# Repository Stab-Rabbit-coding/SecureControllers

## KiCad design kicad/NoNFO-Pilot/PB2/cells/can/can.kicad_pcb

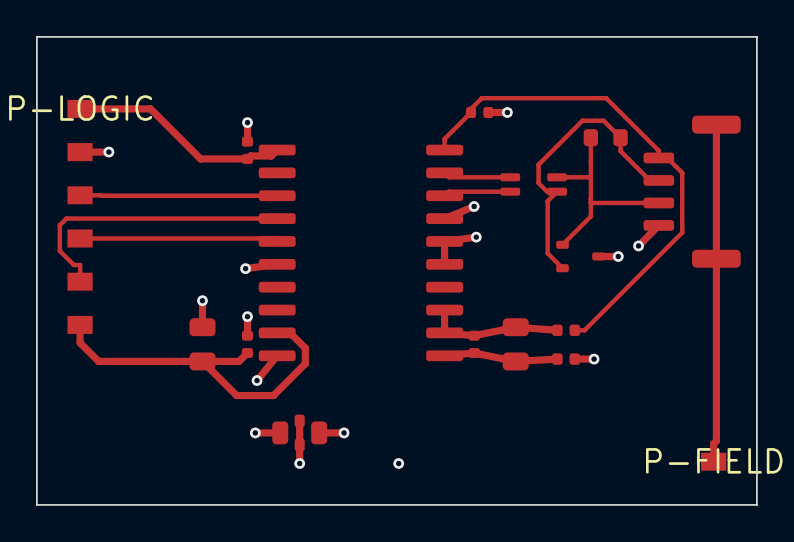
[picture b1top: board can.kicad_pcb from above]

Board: 4 copper layers, 40.0 x 26.0 mm, 16 parts (0 on the bottom side), 15 nets.

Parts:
C-CAN1, C-CAN4: 10nF; C_0402_1005Metric
C-CAN2, C-CAN5: 10uF 10V X5R; C_0805_2012Metric
C-CAN3, C-CAN6: 100nF; C_0402_1005Metric
CAN-FD: SM04B-GHS-TB; JST_GH_SM04B-GHS-TB_1x04-1MP_P1.25mm_Horizontal
CAN-TR: ISOW1044BDFMR; SOIC-20W_7.5x12.8mm_P1.27mm
CHK-CAN: SRF2012-100Y; Bourns_SRF2012_4T
FB-CAN-G: 330R@100MHz; L_0402_1005Metric
FB-CAN-V: 330R@100MHz; L_0402_1005Metric
P-FIELD: cell port; Port_1x1
P-LOGIC: cell port; Port_6x1
R-CANT: 120R; R_0603_1608Metric
TVS-CAN: ESD2CAN24-Q1; SOT-323_SC-70
X2Y-CAN: 4.7nF X2Y; X2Y_0805_4T

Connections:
+3V3: C-CAN3.1, CAN-TR.1, P-LOGIC.1
+5V: C-CAN1.1, C-CAN2.1, CAN-TR.9, P-LOGIC.6
CAN_H: CAN-TR.19, CHK-CAN.1
CAN_H_F: CAN-FD.2, CHK-CAN.2, R-CANT.1, TVS-CAN.1
CAN_L: CAN-TR.18, CHK-CAN.4
CAN_L_F: CAN-FD.3, CHK-CAN.3, R-CANT.2, TVS-CAN.2
CAN_STB: CAN-TR.4, P-LOGIC.5
GND: C-CAN1.2, C-CAN2.2, C-CAN3.2, CAN-TR.6, CAN-TR.10, P-LOGIC.2, X2Y-CAN.1, X2Y-CAN.2
GND2_CAN: C-CAN6.2, CAN-FD.1, CAN-TR.15, CAN-TR.16, CAN-TR.17, FB-CAN-G.2, TVS-CAN.3, X2Y-CAN.3, X2Y-CAN.4
GND2_CAN_DCDC: C-CAN4.2, C-CAN5.2, CAN-TR.11, FB-CAN-G.1
MCAN_RX: CAN-TR.5, P-LOGIC.4
MCAN_TX: CAN-TR.3, P-LOGIC.3
PGND: CAN-FD.MP, P-FIELD.1
VCC2_CAN: C-CAN6.1, CAN-FD.4, CAN-TR.20, FB-CAN-V.2
VCC2_CAN_DCDC: C-CAN4.1, C-CAN5.1, CAN-TR.12, CAN-TR.13, FB-CAN-V.1

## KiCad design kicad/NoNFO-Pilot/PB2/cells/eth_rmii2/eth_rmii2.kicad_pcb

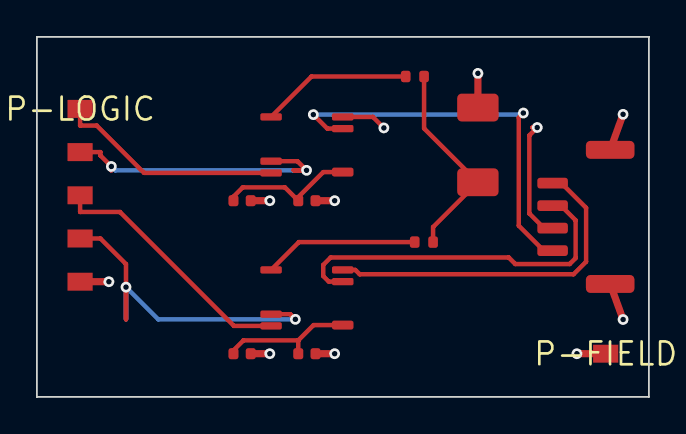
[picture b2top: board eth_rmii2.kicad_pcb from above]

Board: 4 copper layers, 34.0 x 20.0 mm, 12 parts (0 on the bottom side), 15 nets.

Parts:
C-RMII2-BS: 10nF 2kV; C_1808_4520Metric
C-RMII2-CRD1, C-RMII2-CTD1: 100nF; C_0402_1005Metric
C-RMII2-CRD2, C-RMII2-CTD2: 1uF; C_0402_1005Metric
J-ETH-RMII2: SM04B-GHS-TB; JST_GH_SM04B-GHS-TB_1x04-1MP_P1.25mm_Horizontal
P-FIELD: cell port; Port_1x1
P-LOGIC: cell port; Port_5x1
R-RMII2-BSR, R-RMII2-BST: 75R; R_0402_1005Metric
T-RMII2-RX, T-RMII2-TX: TC1G00; Pulse_TC1G00_PulseChip_4.7x3.2mm

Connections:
ETH_RMII2_BS: C-RMII2-BS.1, R-RMII2-BSR.2, R-RMII2-BST.2
ETH_RMII2_CRD: C-RMII2-CRD1.1, C-RMII2-CRD2.1, T-RMII2-RX.7
ETH_RMII2_CTD: C-RMII2-CTD1.1, C-RMII2-CTD2.1, T-RMII2-TX.7
ETH_RMII2_LINE_CRX: R-RMII2-BSR.1, T-RMII2-RX.3
ETH_RMII2_LINE_CTX: R-RMII2-BST.1, T-RMII2-TX.3
ETH_RMII2_LINE_RXN: J-ETH-RMII2.4, T-RMII2-RX.5
ETH_RMII2_LINE_RXP: J-ETH-RMII2.3, T-RMII2-RX.6
ETH_RMII2_LINE_TXN: J-ETH-RMII2.2, T-RMII2-TX.5
ETH_RMII2_LINE_TXP: J-ETH-RMII2.1, T-RMII2-TX.6
ETH_RMII2_RXN: P-LOGIC.4, T-RMII2-RX.2
ETH_RMII2_RXP: P-LOGIC.3, T-RMII2-RX.1
ETH_RMII2_TXN: P-LOGIC.2, T-RMII2-TX.2
ETH_RMII2_TXP: P-LOGIC.1, T-RMII2-TX.1
GND: C-RMII2-CRD1.2, C-RMII2-CRD2.2, C-RMII2-CTD1.2, C-RMII2-CTD2.2, P-LOGIC.5
PGND: C-RMII2-BS.2, J-ETH-RMII2.MP, P-FIELD.1

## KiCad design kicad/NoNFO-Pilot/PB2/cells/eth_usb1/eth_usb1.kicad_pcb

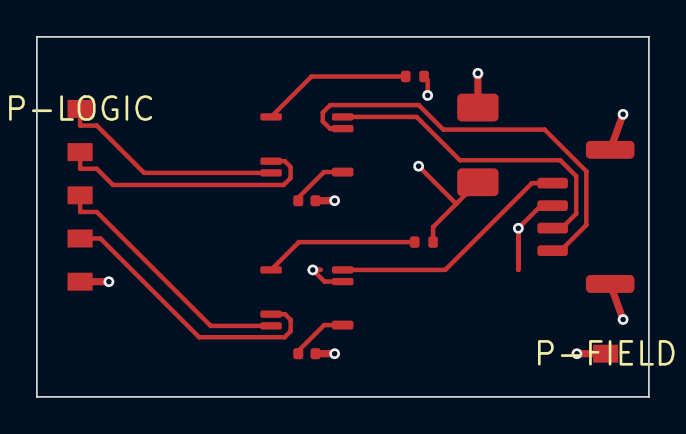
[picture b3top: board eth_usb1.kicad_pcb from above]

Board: 4 copper layers, 34.0 x 20.0 mm, 10 parts (0 on the bottom side), 15 nets.

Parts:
C-USB1-BS: 10nF 2kV; C_1808_4520Metric
C-USB1-CRD, C-USB1-CTD: 100nF; C_0402_1005Metric
J-ETH-USB1: SM04B-GHS-TB; JST_GH_SM04B-GHS-TB_1x04-1MP_P1.25mm_Horizontal
P-FIELD: cell port; Port_1x1
P-LOGIC: cell port; Port_5x1
R-USB1-BSR, R-USB1-BST: 75R; R_0402_1005Metric
T-USB1-RX, T-USB1-TX: TC1G00; Pulse_TC1G00_PulseChip_4.7x3.2mm

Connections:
ETH_USB1_BS: C-USB1-BS.1, R-USB1-BSR.2, R-USB1-BST.2
ETH_USB1_CRD: C-USB1-CRD.1, T-USB1-RX.7
ETH_USB1_CTD: C-USB1-CTD.1, T-USB1-TX.7
ETH_USB1_LINE_CRX: R-USB1-BSR.1, T-USB1-RX.3
ETH_USB1_LINE_CTX: R-USB1-BST.1, T-USB1-TX.3
ETH_USB1_LINE_RXN: J-ETH-USB1.4, T-USB1-RX.5
ETH_USB1_LINE_RXP: J-ETH-USB1.3, T-USB1-RX.6
ETH_USB1_LINE_TXN: J-ETH-USB1.2, T-USB1-TX.5
ETH_USB1_LINE_TXP: J-ETH-USB1.1, T-USB1-TX.6
ETH_USB1_RXN: P-LOGIC.4, T-USB1-RX.2
ETH_USB1_RXP: P-LOGIC.3, T-USB1-RX.1
ETH_USB1_TXN: P-LOGIC.2, T-USB1-TX.2
ETH_USB1_TXP: P-LOGIC.1, T-USB1-TX.1
GND: C-USB1-CRD.2, C-USB1-CTD.2, P-LOGIC.5
PGND: C-USB1-BS.2, J-ETH-USB1.MP, P-FIELD.1

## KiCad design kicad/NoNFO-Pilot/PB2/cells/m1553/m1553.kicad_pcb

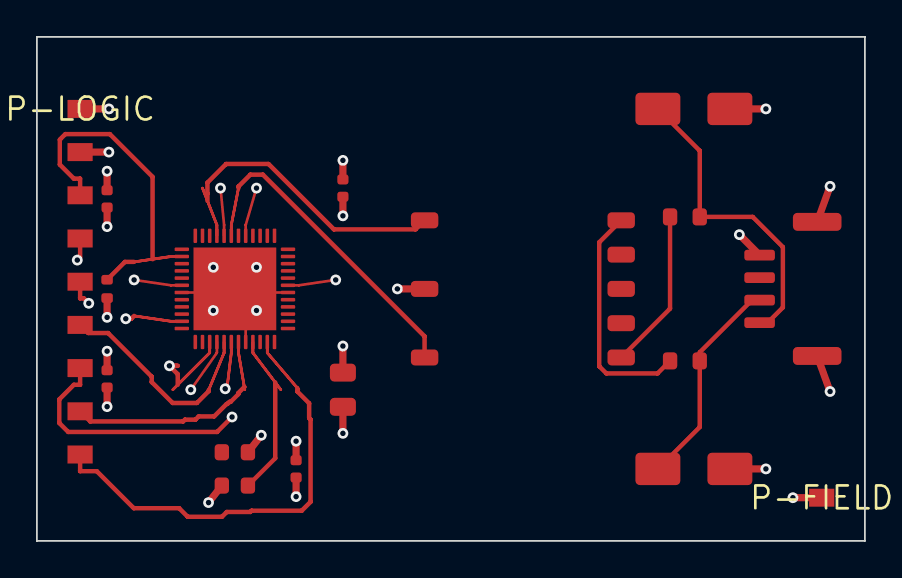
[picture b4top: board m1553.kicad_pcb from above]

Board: 4 copper layers, 46.0 x 28.0 mm, 16 parts (0 on the bottom side), 17 nets.

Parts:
1553-XCVR: HI-6138PCIF; Holt_HI-6138_QFN-48_6x6mm_P0.4mm_EP4.6mm
1553-XFM: PM-DB2791S; Xfmr_1553_SMD_0.40in_8pin
C-50M, C-1553A, C-1553B, C-1553D: 100nF; C_0402_1005Metric
C-1553C: 10uF 6.3V X5R; C_0805_2012Metric
MIL-1553: SM04B-GHS-TB; JST_GH_SM04B-GHS-TB_1x04-1MP_P1.25mm_Horizontal
P-FIELD: cell port; Port_1x1
P-LOGIC: cell port; Port_9x1
R-1553IRQ: 10k; R_0402_1005Metric
R-1553N, R-1553P: 55R 2%; R_0603_1608Metric
TVS-1553N, TVS-1553P: SMAJ33CA; D_SMA
X-50M: 50MHz 3.3V; Oscillator_SMD_ECS_2520MV-xxx-xx-4Pin_2.5x2.0mm

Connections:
+3V3: 1553-XCVR.6, 1553-XCVR.16, 1553-XCVR.31, 1553-XCVR.41, 1553-XCVR.44, C-50M.1, C-1553A.1, C-1553B.1, C-1553C.1, C-1553D.1, P-LOGIC.1, R-1553IRQ.1, X-50M.4
BUS_1553_N: MIL-1553.2, R-1553N.2, TVS-1553N.1
BUS_1553_P: MIL-1553.1, R-1553P.2, TVS-1553P.1
GND: 1553-XCVR.7, 1553-XCVR.20, 1553-XCVR.30, 1553-XCVR.49, 1553-XFM.2, C-50M.2, C-1553A.2, C-1553B.2, C-1553C.2, C-1553D.2, P-LOGIC.2, X-50M.2
M1553_CSN: 1553-XCVR.15, P-LOGIC.5
M1553_IRQN: 1553-XCVR.2, P-LOGIC.3, R-1553IRQ.2
M1553_MCLK: 1553-XCVR.21, X-50M.3
M1553_MISO: 1553-XCVR.18, P-LOGIC.7
M1553_MOSI: 1553-XCVR.19, P-LOGIC.8
M1553_MRN: 1553-XCVR.23, P-LOGIC.9
M1553_N: 1553-XCVR.43, 1553-XFM.3
M1553_P: 1553-XCVR.45, 1553-XFM.1
M1553_SCK: 1553-XCVR.17, P-LOGIC.6
M1553_SEC_N: 1553-XFM.8, R-1553N.1
M1553_SEC_P: 1553-XFM.4, R-1553P.1
M1553_TX_INH: 1553-XCVR.11, P-LOGIC.4
PGND: MIL-1553.4, MIL-1553.MP, P-FIELD.1, TVS-1553N.2, TVS-1553P.2
